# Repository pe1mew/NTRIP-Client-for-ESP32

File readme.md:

# NTRIP-Client-for-ESP32.

This repository contains the progress in developing a NTRIP client on a ESP32 for the HAN Hydromotive racingteam. 

## License and disclaimer. 

Please note the license at the end of this document. 

# License
This project is free: You can redistribute it and/or modify it under the terms of a Creative Commons Attribution-NonCommercial 4.0 International License (http://creativecommons.org/licenses/by-nc/4.0/) by Remko Welling (https://ese.han.nl/~rwelling) E-mail: remko.welling@han.nl

<br />This work is licensed under a <a rel="license" href="http://creativecommons.org/licenses/by-nc/4.0/">Creative Commons Attribution-NonCommercial 4.0 International License</a>.

# Disclaimer
This project is distributed in the hope that it will be useful, but WITHOUT ANY WARRANTY; without even the implied warranty of MERCHANTABILITY or FITNESS FOR A PARTICULAR PURPOSE.

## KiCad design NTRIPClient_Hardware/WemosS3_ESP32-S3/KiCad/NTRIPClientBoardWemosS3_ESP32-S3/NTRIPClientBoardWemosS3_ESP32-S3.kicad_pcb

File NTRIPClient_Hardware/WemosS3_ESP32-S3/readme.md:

# Wemos S3 ESP32-S3 Development Board

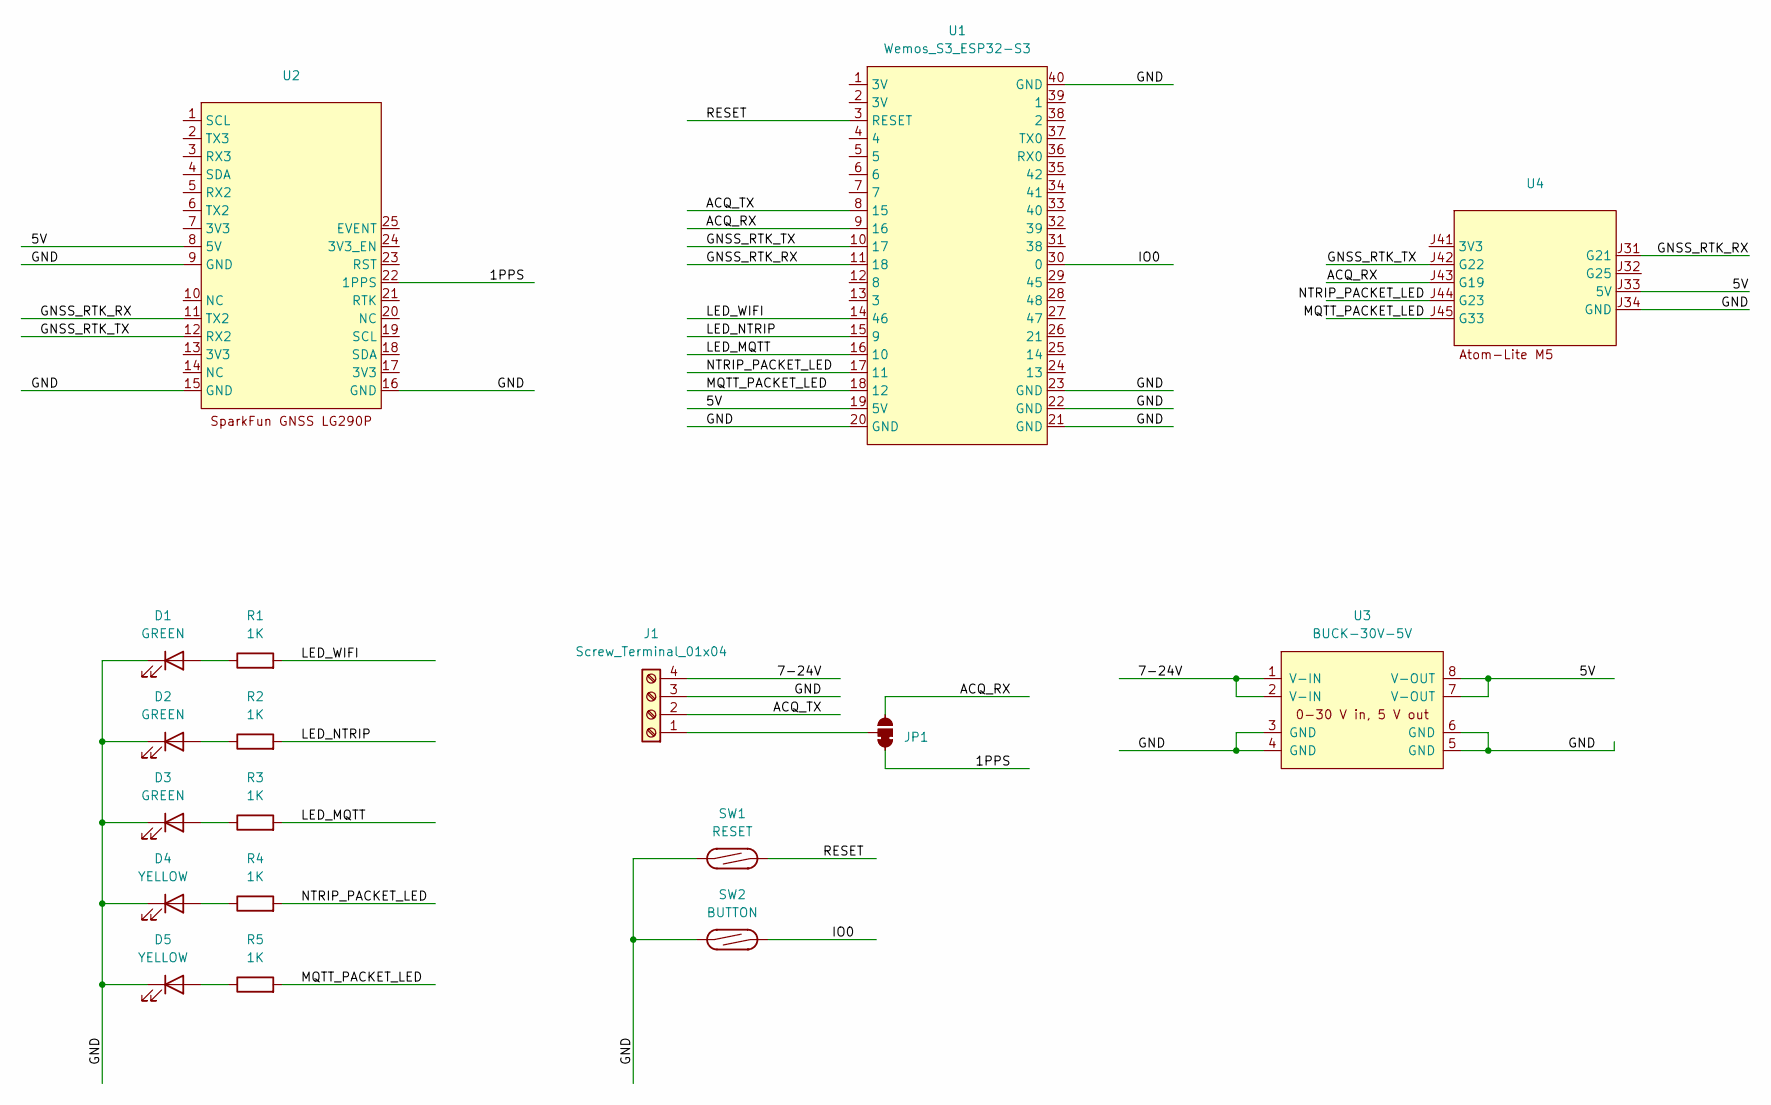
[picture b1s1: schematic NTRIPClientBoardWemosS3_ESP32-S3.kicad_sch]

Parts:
D1, D2, D3: GREEN; LED_1206_3216Metric
D4, D5: YELLOW; LED_1206_3216Metric
J1: Screw_Terminal_01x04; PhoenixContact_MSTBVA_2,5_4-G_1x04_P5.00mm_Vertical
JP1: Jumper_3_NC-1_Trace
R1, R2, R3, R4, R5: 1K; R_1206_3216Metric
SW1: RESET; SW_SPST_REED_20mm
SW2: BUTTON; SW_SPST_REED_20mm
U1: Wemos_S3_ESP32-S3
U2: SparkFun_GNSS_LG290P
U3: BUCK-30V-5V
U4: Atom-Lite_M5

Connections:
/1PPS: JP1.1 (A), U2.22 (1PPS)
/5V: U1.19 (5V), U2.8 (5V), U3.7 (V-OUT), U3.8 (V-OUT), U4.J33 (5V)
/7-24V: J1.4, U3.1 (V-IN), U3.2 (V-IN)
/ACQ_RX: JP1.3 (C), U1.9 (16), U4.J43 (G19)
/ACQ_TX: J1.2, U1.8 (15)
/GND: D1.1 (K), D2.1 (K), D3.1 (K), D4.1 (K), D5.1 (K), J1.3, SW1.1, SW2.1, U1.20 (GND), U1.21 (GND), U1.22 (GND), U1.23 (GND), U1.40 (GND), U2.9 (GND), U2.15 (GND), U2.16 (GND), U3.3 (GND), U3.4 (GND), U3.5 (GND), U3.6 (GND), U4.J34 (GND)
/GNSS_RTK_RX: U1.11 (18), U2.11 (TX2), U4.J31 (G21)
/GNSS_RTK_TX: U1.10 (17), U2.12 (RX2), U4.J42 (G22)
/IO0: SW2.2, U1.30 (0)
/LED_MQTT: R3.2, U1.16 (10)
/LED_NTRIP: R2.2, U1.15 (9)
/LED_WIFI: R1.2, U1.14 (46)
/MQTT_PACKET_LED: R5.2, U1.18 (12), U4.J45 (G33)
/NTRIP_PACKET_LED: R4.2, U1.17 (11), U4.J44 (G23)
/RESET: SW1.2, U1.3 (RESET)
unnamed: D1.2 (A), R1.1
unnamed: D2.2 (A), R2.1
unnamed: D3.2 (A), R3.1
unnamed: D4.2 (A), R4.1
unnamed: D5.2 (A), R5.1
unnamed: J1.1, JP1.2 (B)

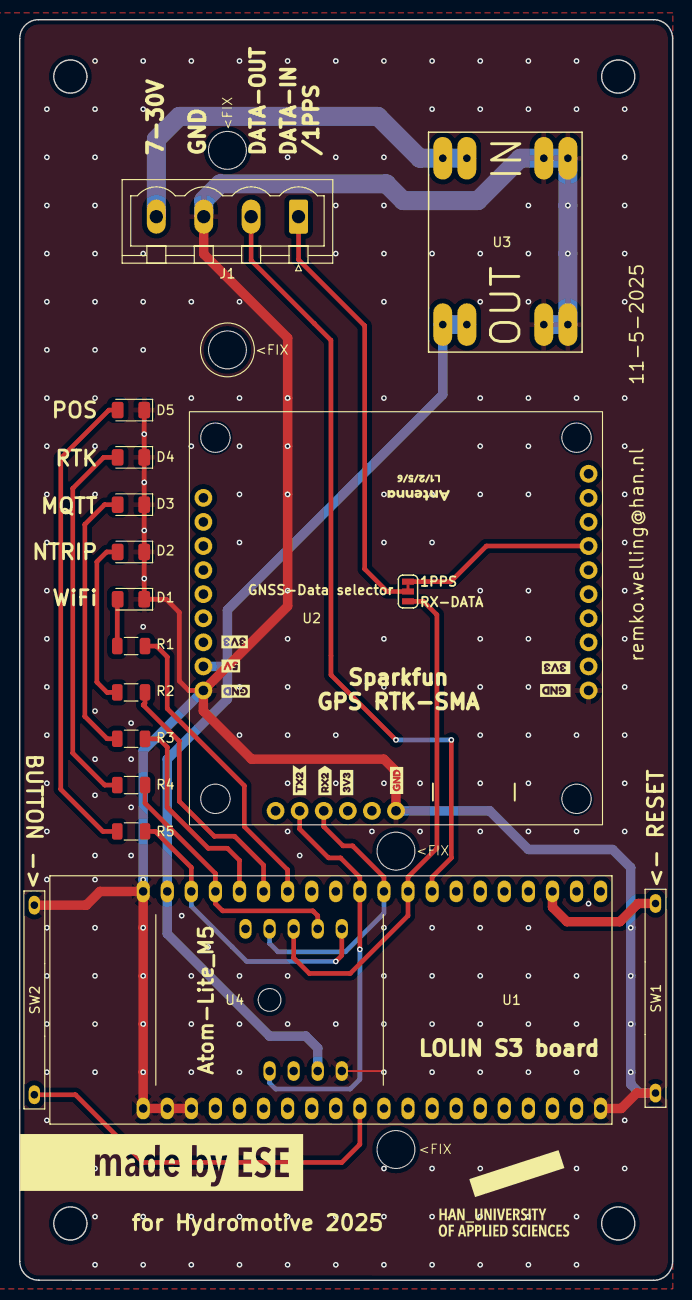
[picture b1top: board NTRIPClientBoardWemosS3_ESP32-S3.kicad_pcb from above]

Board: 2 copper layers, 68.9 x 133.0 mm, 18 parts (0 on the bottom side), 21 nets.

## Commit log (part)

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2025-03-21 Added files to nurse the project in git
2025-03-21 Modified SPIFFS files and instructions.
2025-03-21 Working code with led indication of progress
2025-03-21 Working portal. Starts in normal operation after 3 sec. button press, at boot when pressing the button.
2025-03-21 Some commit
2025-03-21 addded .gitignore
2025-03-21 Finalize code
2025-03-23 Working version that works with Quectel LG290P at 460800 bps on Atom Lite
2025-03-23 Some updates
2025-03-23 start of adding MQTT client
2025-03-24 Some changes and additions to make MQTT client work
2025-03-24 Added working MQTT client and functions to compose position json with relevant data
2025-03-25 Finalized first set of requirements, Start of documentation.
2025-03-26 Refactoring directory structure
2025-03-26 start documentation on ESP32-S3-Pico
2025-03-26 Updated Documentation
2025-03-26 Update documentation and add submodule for Wemos boards
2025-03-26 Added initial KiCad schema
2025-03-26 remove unnecessary library
2025-03-26 Added my kicad library as submodule
2025-03-26 Change organization on mylibrary for KiCad
2025-03-26 Added Kicad component
2025-03-27 Added component and footprint to KiCad
2025-03-28 Added NTRIP client documentation: Manual
2025-03-29 Update documentation
2025-03-29 Added documentation and composite message with date-time.
2025-03-29 correction
2025-03-30 Update unit test CRC16 calculation
2025-03-30 Finalized unit-test of CRC-16 calculation function.
2025-03-30 Enhanced unit test process in main.cpp
2025-03-30 Start drawing PCB
2025-04-02 updated NMEA parsing and added correction
2025-04-02 Solved issue with parsing of NMEA sentences, added age of correction data, and updated documentation
2025-04-06 Release 0.0.1
2025-04-12 First version of software for LOLIN S3
2025-04-13 Updated PCB for LOLIN S3 WEMOS board to version 1.0
2025-04-30 refactored code, moved hard- and software settings to separate file hardwareConfig.h, moved CRC calculation function to a external header and implementation file.
2025-05-09 Update code base to version 0.9 for debugging speed issue.
2025-05-09 Solved issue with speed and made solution independent form GNSS receiver
2025-05-09 Update to 0.9.2, added DTR for logger
2025-05-09 Corrected time use 2 or 3 characters for milliseconds
2025-05-10 corrected request of mount points so they will be provided when using credentials to the caster
2025-05-11 corrected request of mount points so they will be provided when using credentials to the caster Added Atom-Lite M5 to PCB design
2025-05-11 Updated documentation and code
2025-05-11 Added first attempt for NMEA parser
2025-05-26 Added Byte stuffing to compose message function
2025-06-05 Corrected software for PCB, removed blocking parts to start immediate sending of time removed AP
2025-06-06 changed wifi to nonBlocking added verification of valid data in nmea parser
2025-06-10 Added continous sending of GGA
2025-06-20 corrected wifi password management
2026-01-12 some update
